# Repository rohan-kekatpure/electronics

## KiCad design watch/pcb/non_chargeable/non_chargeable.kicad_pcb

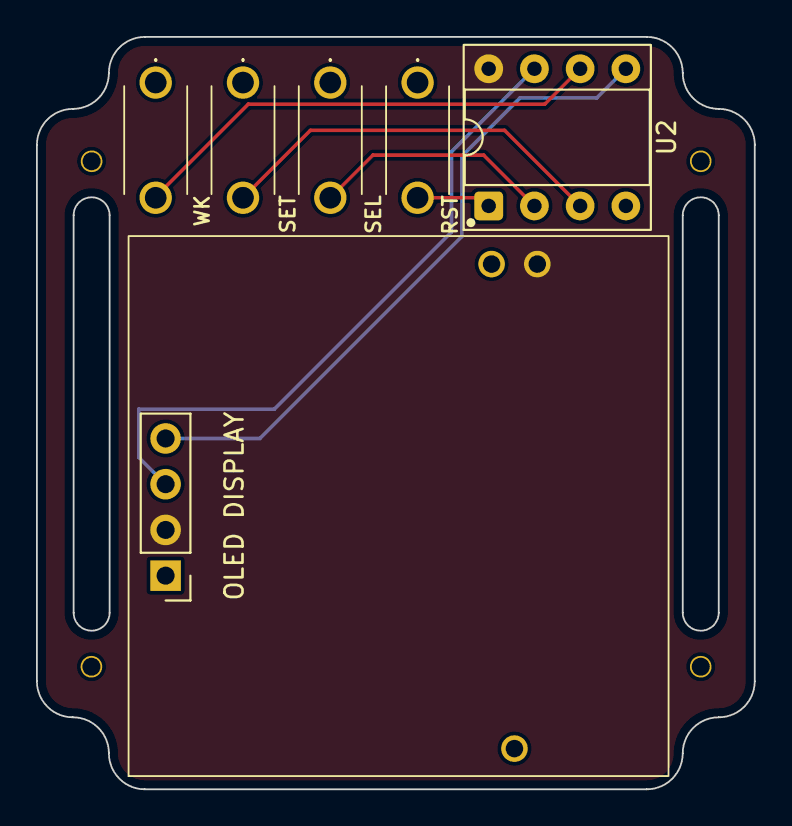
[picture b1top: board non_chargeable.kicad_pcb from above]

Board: 2 copper layers, 39.9 x 41.8 mm, 11 parts (1 on the bottom side), 8 nets.

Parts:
BT2: 1059; BatteryHolder_Keystone_1059_THT
H1, H2, H3, H4: MountingHole; Circular_Mounting_Hole_1mmDia
OLED_DISPLAY1: OLED DISPLAY; SSD1306_OLED_Display_128x64
RST: RST; PTS636_SM43_LFS
SEL: SEL; PTS636_SM43_LFS
SET: SET; PTS636_SM43_LFS
U2: ATTINY85-20SUR; DIP-8_W7.62mm_Socket
WK: WK; PTS636_SM43_LFS

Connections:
GND: BT2.N, OLED_DISPLAY1.1 (GND), RST.1, SEL.1, SET.1, U2.4 (GND), WK.1
RESET: RST.2, U2.1 (PB5)
SCK: OLED_DISPLAY1.3 (SCK), U2.7 (PB2)
SDA: OLED_DISPLAY1.4 (SDA), U2.5 (PB0)
SELECT: SEL.2, U2.2 (PB3)
SET: SET.2, U2.3 (PB4)
VCC: BT2.P1, OLED_DISPLAY1.2 (VCC), U2.8 (VCC)
WAKE: U2.6 (PB1), WK.2

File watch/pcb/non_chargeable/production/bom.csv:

Designator,Footprint,Quantity,Value,LCSC Part #
BT2,BatteryHolder_Keystone_1059_THT,1,1059,
"H1, H2, H3, H4",Circular_Mounting_Hole_1mmDia,4,MountingHole,
OLED_DISPLAY1,SSD1306_OLED_Display_128x64,1,OLED DISPLAY,
RST,PTS636_SM43_LFS,1,RST,C2689642
SEL,PTS636_SM43_LFS,1,SEL,C2689642
SET,PTS636_SM43_LFS,1,SET,C2689642
U2,DIP-8_W7.62mm_Socket,1,ATTINY85-20SUR,C31540447
WK,PTS636_SM43_LFS,1,WK,C2689642

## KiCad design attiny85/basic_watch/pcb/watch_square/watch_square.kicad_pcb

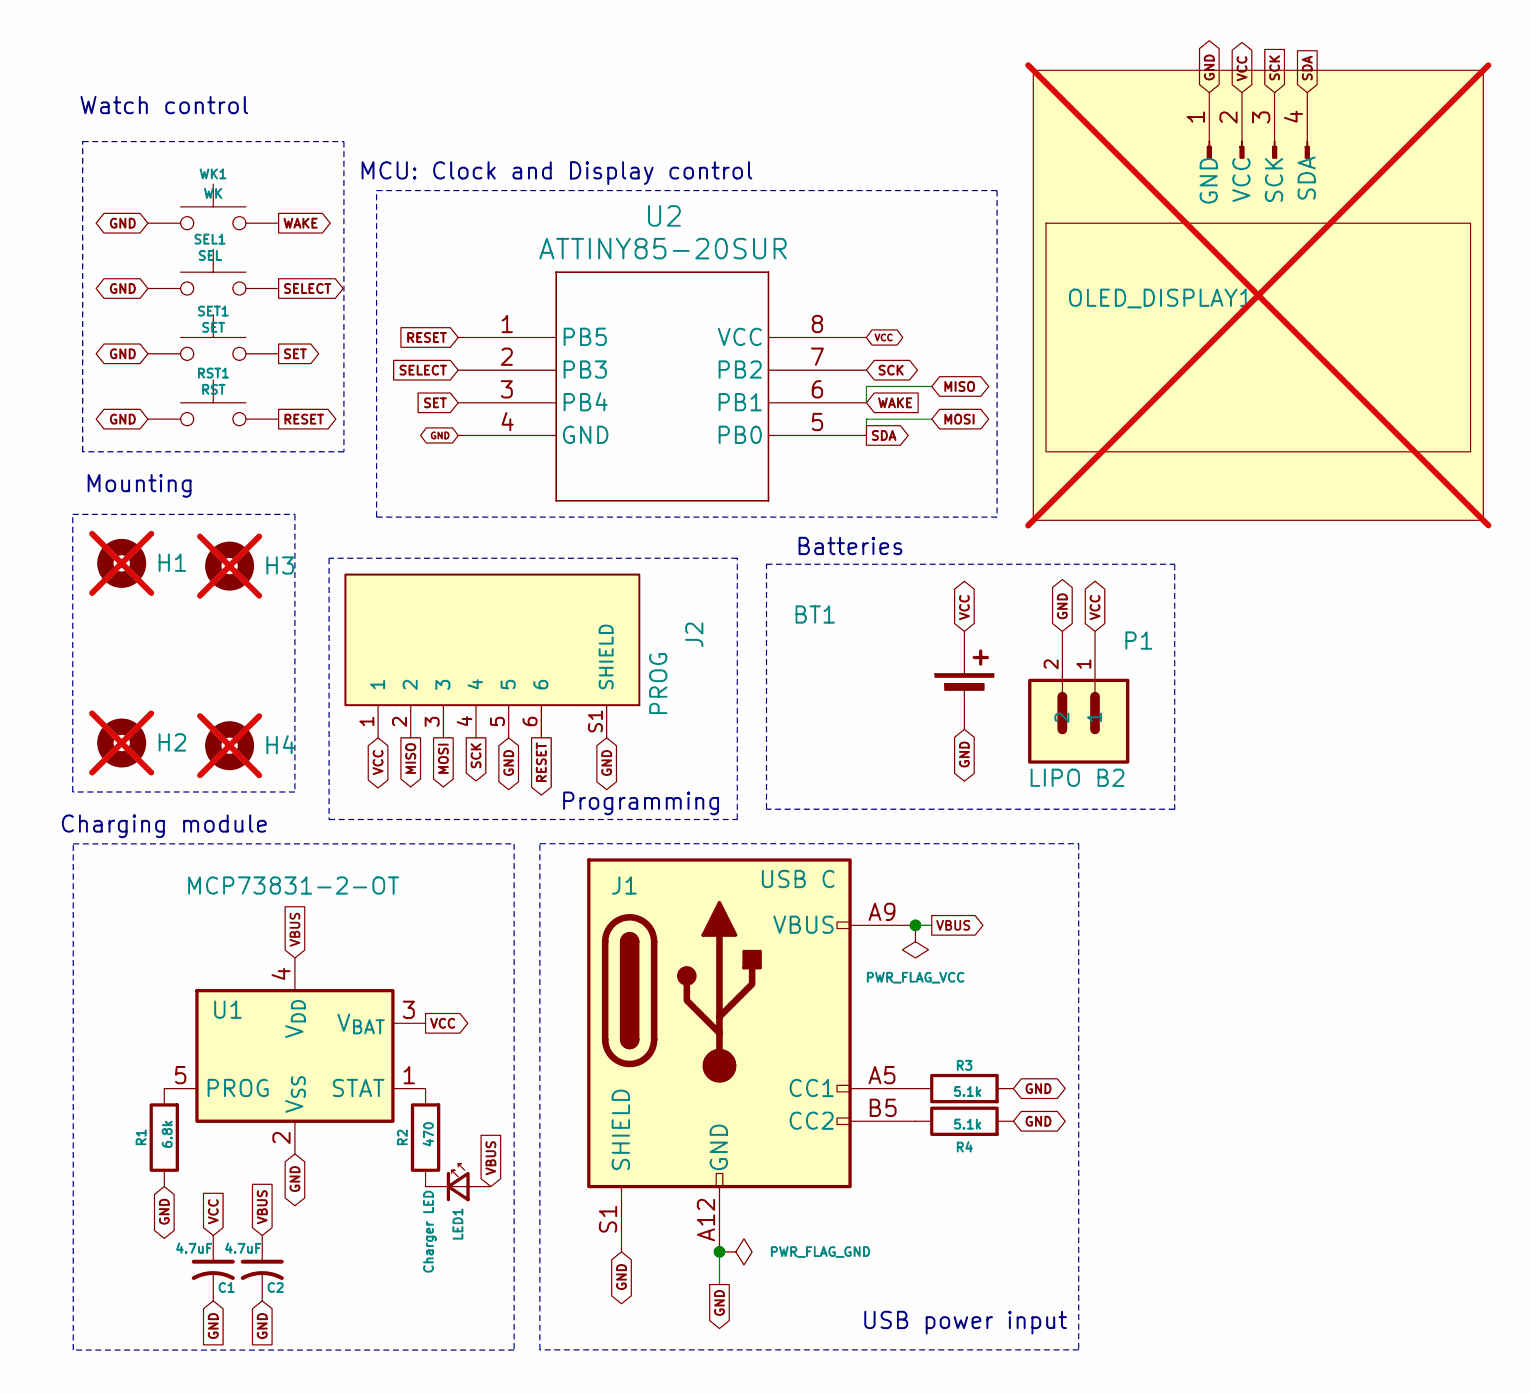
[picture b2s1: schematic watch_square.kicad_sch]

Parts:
BT1: BT1; BatteryHolder_Keystone_1060_1x2032; LCSC C238069
C1, C2: 4.7uF; C_0805_2012Metric; LCSC C380343
H1, H2, H3, H4: MountingHole; Circular_Mounting_Hole_1mmDia; not fitted
J1: USB C; USB_C_Receptacle_GCT_USB4125-xx-x-0190_6P_TopMnt_Horizontal; LCSC C7507406
J2: PROG; JST_PH_1x06_2mm_horizontal.pretty; LCSC C265405
LED1: Charger LED; LED_0805_2012Metric_Pad1.15x1.40mm_HandSolder; LCSC C19171391
OLED_DISPLAY1: OLED DISPLAY; SSD1306_OLED_Display_128x64; not fitted
P1: LIPO B2; JST_PH_1x02_2mm_horizontal; LCSC C295747
R1: 6.8k; R_0805_2012Metric; LCSC C17772
R2: 470; R_0805_2012Metric; LCSC C2907329
R3, R4: 5.1k; R_0805_2012Metric; LCSC C2930296
RST1: RST; SW_Tactile_SPST_NO_Straight_CK_PTS636Sx25SMTRLFS; MFR part PTS636SK25SMTRLFS; LCSC C2689642
SEL1: SEL; SW_Tactile_SPST_NO_Straight_CK_PTS636Sx25SMTRLFS; MFR part PTS636SK25SMTRLFS; LCSC C2689642
SET1: SET; SW_Tactile_SPST_NO_Straight_CK_PTS636Sx25SMTRLFS; MFR part PTS636SK25SMTRLFS; LCSC C2689642
U1: MCP73831-2-OT; SOT-23-5; LCSC C424093
U2: ATTINY85-20SUR; 8S2_ATM-L; LCSC C31540447
WK1: WK; SW_Tactile_SPST_NO_Straight_CK_PTS636Sx25SMTRLFS; MFR part PTS636SK25SMTRLFS; LCSC C2689642

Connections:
GND: BT1.2 (-), C1.2, C2.2, J1.A12 (GND), J1.B12 (GND), J1.S1 (SHIELD), J2.5, J2.S1 (SHIELD), J2.S2 (SHIELD), OLED_DISPLAY1.1 (GND), P1.2, R1.1, R3.2, R4.2, RST1.1, SEL1.1, SET1.1, U1.2 (V_{SS}), U2.4 (GND), WK1.1
MISO: J2.2, U2.6 (PB1), WK1.2
MOSI: J2.3, OLED_DISPLAY1.4 (SDA), U2.5 (PB0)
unnamed: J1.A5 (CC1), R3.1
unnamed: J1.B5 (CC2), R4.1
unnamed: LED1.1 (K), R2.1
unnamed: R1.2, U1.5 (PROG)
unnamed: R2.2, U1.1 (STAT)
RESET: J2.6, RST1.2, U2.1 (PB5)
SCK: J2.4, OLED_DISPLAY1.3 (SCK), U2.7 (PB2)
SELECT: SEL1.2, U2.2 (PB3)
SET: SET1.2, U2.3 (PB4)
VBUS: C2.1, J1.A9 (VBUS), J1.B9 (VBUS), LED1.2 (A), U1.4 (V_{DD})
VCC: BT1.1 (+), C1.1, J2.1, OLED_DISPLAY1.2 (VCC), P1.1, U1.3 (V_{BAT}), U2.8 (VCC)

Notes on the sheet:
Batteries
Mounting
Charging module
Programming
MCU: Clock and Display control
Watch control
USB power input

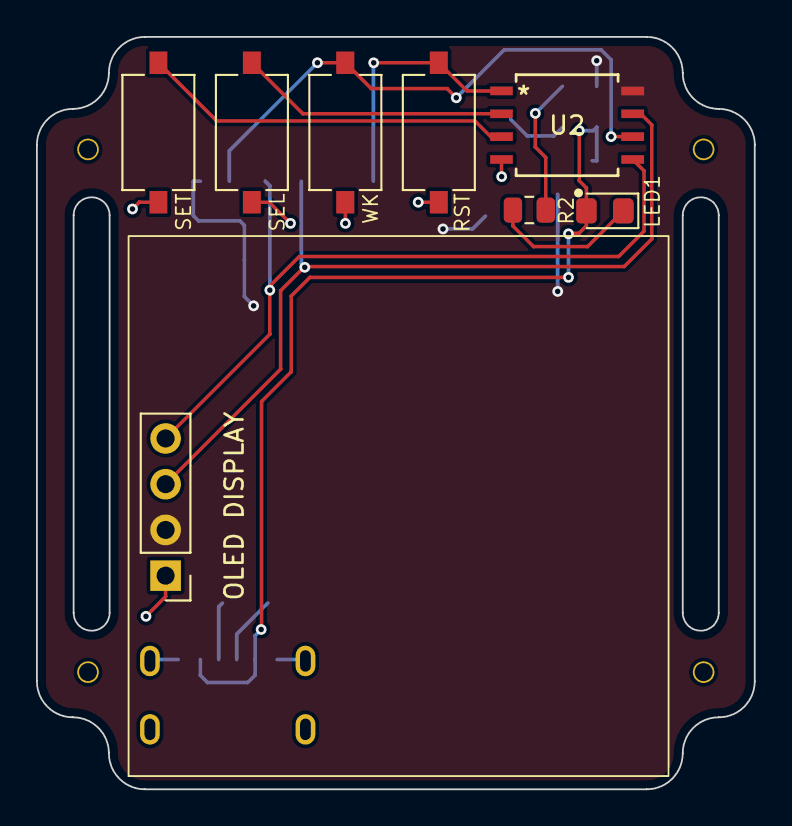
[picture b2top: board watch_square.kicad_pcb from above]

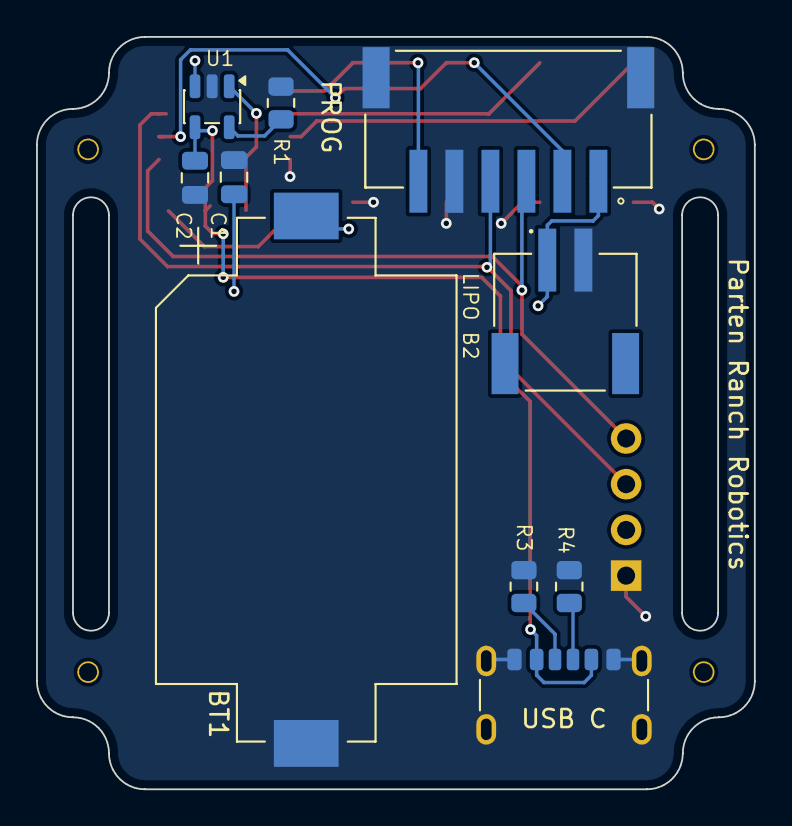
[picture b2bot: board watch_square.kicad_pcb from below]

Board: 2 copper layers, 39.9 x 41.8 mm, 22 parts (10 on the bottom side), 14 nets.

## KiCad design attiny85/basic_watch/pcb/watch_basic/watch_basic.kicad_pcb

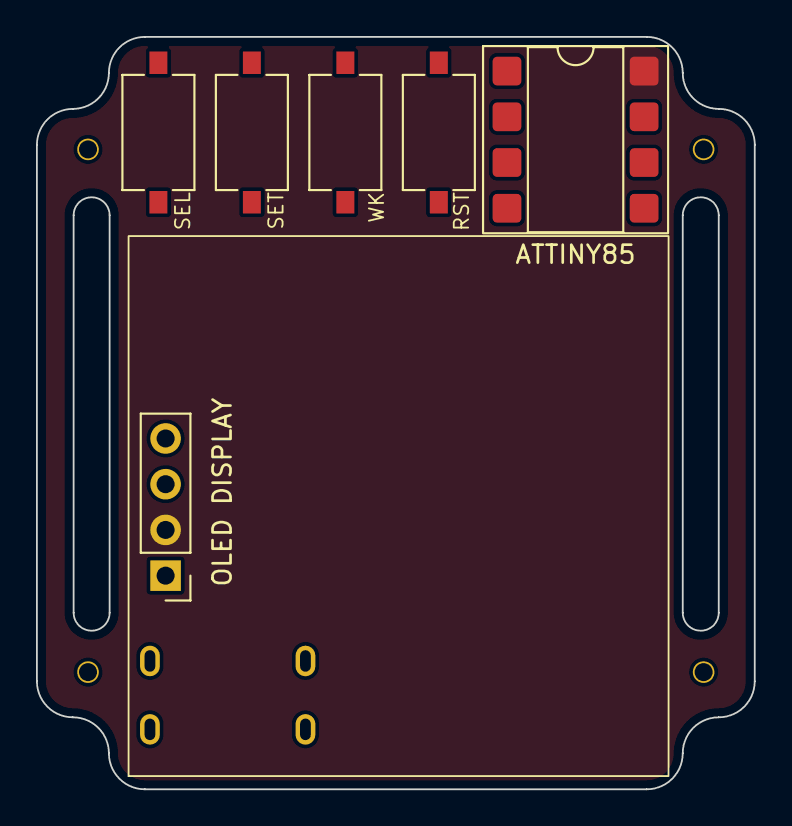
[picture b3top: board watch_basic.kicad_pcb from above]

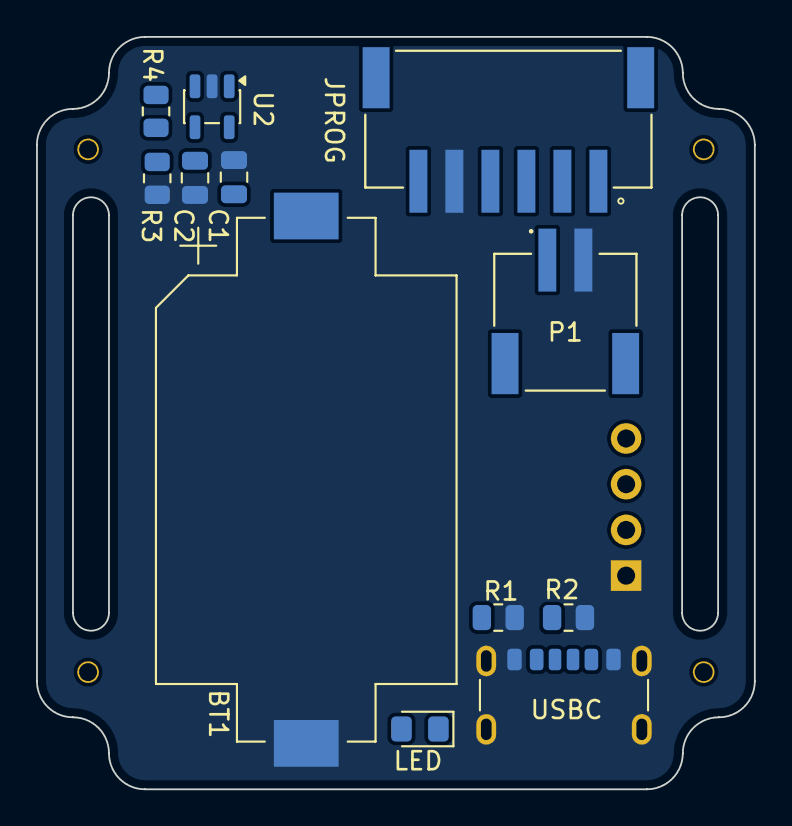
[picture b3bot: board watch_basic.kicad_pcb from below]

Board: 2 copper layers, 39.9 x 41.8 mm, 22 parts (12 on the bottom side), 15 nets, no tracks yet.

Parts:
ATTINY85: ATTINY85; DIP-8_W7.62mm_SMDSocket_SmallPads
BT1: Battery_Cell; BatteryHolder_Keystone_1060_1x2032
C1, C2: 4.7uF; C_0805_2012Metric
H1, H2, H3, H4: MountingHole; Circular_Mounting_Hole_1mmDia
JPROG: Programmer; JST_PH_1x06_2mm_horizontal.pretty
LED: Charger LED; LED_0805_2012Metric_Pad1.15x1.40mm_HandSolder
OLED DISPLAY: SSD1306_OLED_Display_128x64
P1: JST_LIPO; JST_PH_1x02_2mm_horizontal
R1, R2: 5.1k; R_0805_2012Metric
R3: 6.8k; R_0805_2012Metric
R4: 470; R_0805_2012Metric
RST: Reset; SW_Tactile_SPST_NO_Straight_CK_PTS636Sx25SMTRLFS
SEL: Select; SW_Tactile_SPST_NO_Straight_CK_PTS636Sx25SMTRLFS
SET: Set; SW_Tactile_SPST_NO_Straight_CK_PTS636Sx25SMTRLFS
U2: MCP73831-2-OT; SOT-23-5
USBC: USB C; USB_C_Receptacle_GCT_USB4125-xx-x-0190_6P_TopMnt_Horizontal
WK: Wake; SW_Tactile_SPST_NO_Straight_CK_PTS636Sx25SMTRLFS

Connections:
GND: ATTINY85.4 (GND), BT1.2 (-), C1.2, C2.2, JPROG.5, OLED DISPLAY.1 (GND), P1.2, R1.2, R2.2, R3.1, RST.1, SEL.1, SET.1, U2.2 (V_{SS}), USBC.A12 (GND), USBC.B12 (GND), USBC.S1 (SHIELD), WK.1
MISO: ATTINY85.6 (PB1), JPROG.2, WK.2
MOSI: ATTINY85.5 (AREF/PB0), JPROG.3, OLED DISPLAY.4 (SDA)
unnamed: R1.1, USBC.A5 (CC1)
unnamed: R2.1, USBC.B5 (CC2)
unnamed: JPROG.S1 (SHIELD), JPROG.S2 (SHIELD)
unnamed: LED.1 (K), R4.1
unnamed: R3.2, U2.5 (PROG)
unnamed: R4.2, U2.1 (STAT)
RESET: ATTINY85.1 (~RESET/PB5), JPROG.6, RST.2
SCK: ATTINY85.7 (PB2), JPROG.4, OLED DISPLAY.3 (SCK)
SELECT: ATTINY85.2 (XTAL1/PB3), SEL.2
SET: ATTINY85.3 (XTAL2/PB4), SET.2
VBUS: C2.1, LED.2 (A), U2.4 (V_{DD}), USBC.A9 (VBUS), USBC.B9 (VBUS)
VCC: ATTINY85.8 (VCC), BT1.1 (+), C1.1, JPROG.1, OLED DISPLAY.2 (VCC), P1.1, U2.3 (V_{BAT})

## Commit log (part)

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2024-08-05 Wifi controlled LED
2024-08-05 Refactored the sketch
2024-08-05 added README
2024-08-14 IR LED
2024-08-15 two motor example
2024-08-19 example of basic webserver
2024-08-19 comments
2024-08-19 webserver servestatic
2024-08-21 wifi car
2024-09-02 removed hardcoding of pins
2024-09-03 IR controlled rover
2024-09-05 wifi and ir rover working in fwd and reverse modes
2024-09-06 state update
2024-09-07 RC Rover with restructured code
2024-09-09 circular motion
2024-09-25 disabling motors during direction changes
2024-10-01 RC Rover with memory
2024-10-05 added functions for move execution
2024-10-05 bigfixes
2025-02-17 RC rover v4
2025-02-17 R_Rover_v4
2025-02-22 v5 final version
2025-03-06 smart watch code
2025-03-08 Clock with minute setting button
2025-03-09 Simpler code; HH and MM setting without interrupts
2025-03-10 kicad files for smart watch
2025-03-10 adding a readme
2025-08-23 RC rover final version, working with PCB
2025-08-24 U Turn mode
2025-08-25 BLE and i2c
2025-08-26 basic oled smart watch code; loses significant time due to use of software clock
2025-08-29 clock with hardware timer
2025-10-08 driving OLED ssd1306 using attiny85
2025-10-18 attiny 1 second tick with interrupts
2025-10-26 v0 watch code
2025-10-27 setting datetime working
2025-10-27 datetime update contained in DateTime struct
2025-10-27 bug fix
2025-10-27 OSCCAL calibration
2025-10-28 efficient divisibility check for leap year
2025-10-30 Fine tuning OSCCAL
2025-11-22 display sleep
2025-11-22 using updateSelector()
2025-11-23 enable IDLE mode
2025-11-23 selector with different font sizes
2025-11-23 drawing pattern
2025-11-24 added analog clock to the right side
2025-11-24 weekday and OSCCAL value settable
2025-11-24 fixed bug where changing the `minute` field changed the OSCCAL value
2025-11-24 Ability to change the name string
2025-11-29 PCB mounting
2025-12-03 production files
2025-12-03 removed lock file
2025-12-03 removed cache files
2025-12-08 added programming connection
2025-12-11 watch with straps
2025-12-12 split by basic and charger versions
2025-12-15 Round watch footprint cannot accomodate all components
2026-01-27 changed footprints
2026-01-29 corrected OLED orientation
2026-02-01 folder renaming
2026-02-08 non- chargeable
2026-02-22 removing bug in watch string
2026-02-23 removed graphics code
2026-03-14 added saving state to EEPROM memory and battery status display
2026-03-14 moving the weekdays array outside the function to save memory
2026-03-15 adding MSG to memory
2026-03-29 removed bug in EEPROM saveState function
